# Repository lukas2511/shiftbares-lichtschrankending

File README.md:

# shiftbares-lichtschrankending

Lichtschranken-Platine für unsere Fledermauslichtschranken

Bauteile:
- 8x Phototransistor (??)
- 8x IR-LED (??)
- 8x 100 Ohm (Vorwiderstand für LEDs)
- 8x 10 kOhm (Pull-Up für Phototransistoren)
- 1x 74HC595 (Shift-Register, U74HC595AG, DIP-16)
- 2x 74HC4066 (4-fach Analog-Schalter, M74HC4066B1R, DIP-14)
- 1x BC337 (NPN Transistor, TO-92)
- 1x 1000µF Kondensator (Radial, schräg montiert -> exakte Größe egal)
- 1x 10-pin 2.54mm Stiftleiste 90°-Winkel
- 1x 10-pin 2.54mm Buchsenleiste 90°-Winkel

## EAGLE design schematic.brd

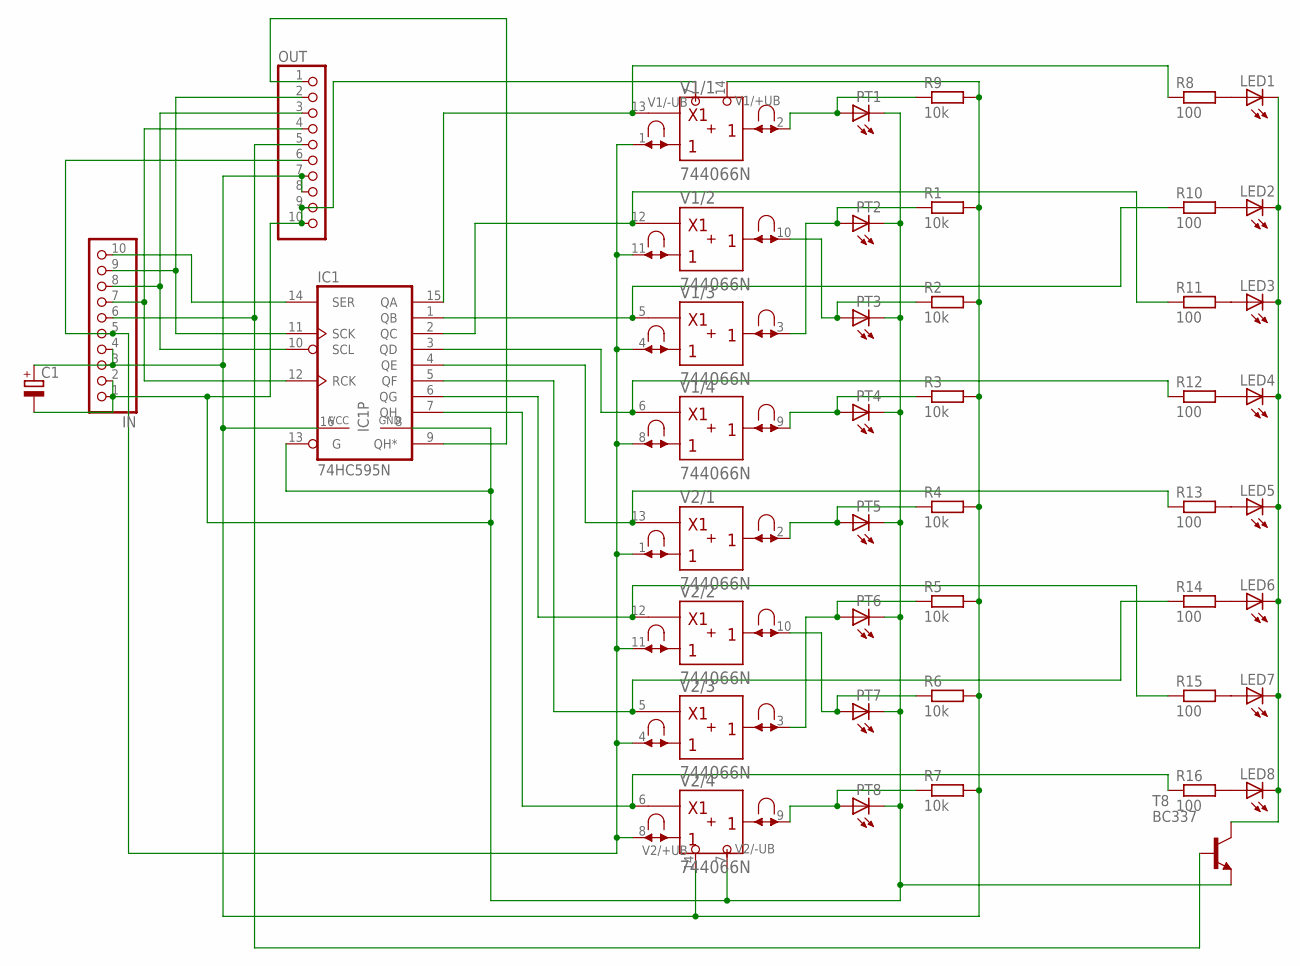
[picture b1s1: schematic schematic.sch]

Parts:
C1: CPOL-EUE5-10.5; E5-10,5
IC1: 74HC595N; DIL16
IN: PINHD-1X10/90; 1X10/90
LED1, LED2, LED3, LED4, LED5, LED6, LED7, LED8: LED5MM
OUT: PINHD-1X10/90; 1X10/90
PT1, PT2, PT3, PT4, PT5, PT6, PT7, PT8: LED5MM
R1, R2, R3, R4, R5, R6, R7, R9: 10k; 0204/7
R8, R10, R11, R12, R13, R14, R15, R16: 100; 0204/7
T8: BC337; TO92
V1, V2: 744066N; DIL14

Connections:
GND: C1.-, IC1.8 (GND), IC1.13 (G), IN.1, IN.2, OUT.9, OUT.10, PT1.K (C), PT2.K (C), PT3.K (C), PT4.K (C), PT5.K (C), PT6.K (C), PT7.K (C), PT8.K (C), T8.1 (E), V1.7 (-UB), V2.7 (-UB)
unnamed: IC1.15 (QA), R8.1, V1.13 (C)
unnamed: IC1.5 (QF), R14.1, V2.5 (C)
unnamed: IN.6, OUT.5, T8.2 (B)
unnamed: IC1.3 (QD), R12.1, V1.6 (C)
unnamed: IC1.4 (QE), R13.1, V2.13 (C)
unnamed: IC1.6 (QG), R15.1, V2.12 (C)
unnamed: IC1.7 (QH), R16.1, V2.6 (C)
unnamed: IC1.9 (QH*), OUT.1
unnamed: IC1.1 (QB), R10.1, V1.5 (C)
unnamed: PT8.A, R7.1, V2.9 (B)
unnamed: PT7.A, R6.1, V2.10 (B)
unnamed: PT6.A, R5.1, V2.3 (B)
unnamed: PT5.A, R4.1, V2.2 (B)
unnamed: PT4.A, R3.1, V1.9 (B)
unnamed: PT3.A, R2.1, V1.10 (B)
unnamed: PT2.A, R1.1, V1.3 (B)
unnamed: PT1.A, R9.1, V1.2 (B)
unnamed: LED1.A, R8.2
unnamed: IC1.10 (SCL), IN.8, OUT.3
unnamed: IC1.12 (RCK), IN.7, OUT.4
unnamed: LED2.A, R10.2
unnamed: IC1.11 (SCK), IN.9, OUT.2
unnamed: IC1.14 (SER), IN.10
unnamed: LED3.A, R11.2
unnamed: LED4.A, R12.2
unnamed: LED5.A, R13.2
unnamed: LED6.A, R14.2
unnamed: LED7.A, R15.2
unnamed: LED8.A, R16.2
unnamed: LED1.K (C), LED2.K (C), LED3.K (C), LED4.K (C), LED5.K (C), LED6.K (C), LED7.K (C), LED8.K (C), T8.3 (C)
unnamed: IC1.2 (QC), R11.1, V1.12 (C)
unnamed: IN.5, OUT.6, V1.1 (A), V1.4 (A), V1.8 (A), V1.11 (A), V2.1 (A), V2.4 (A), V2.8 (A), V2.11 (A)
VCC: C1.+, IC1.16 (VCC), IN.3, IN.4, OUT.7, OUT.8, R1.2, R2.2, R3.2, R4.2, R5.2, R6.2, R7.2, R9.2, V1.14 (+UB), V2.14 (+UB)

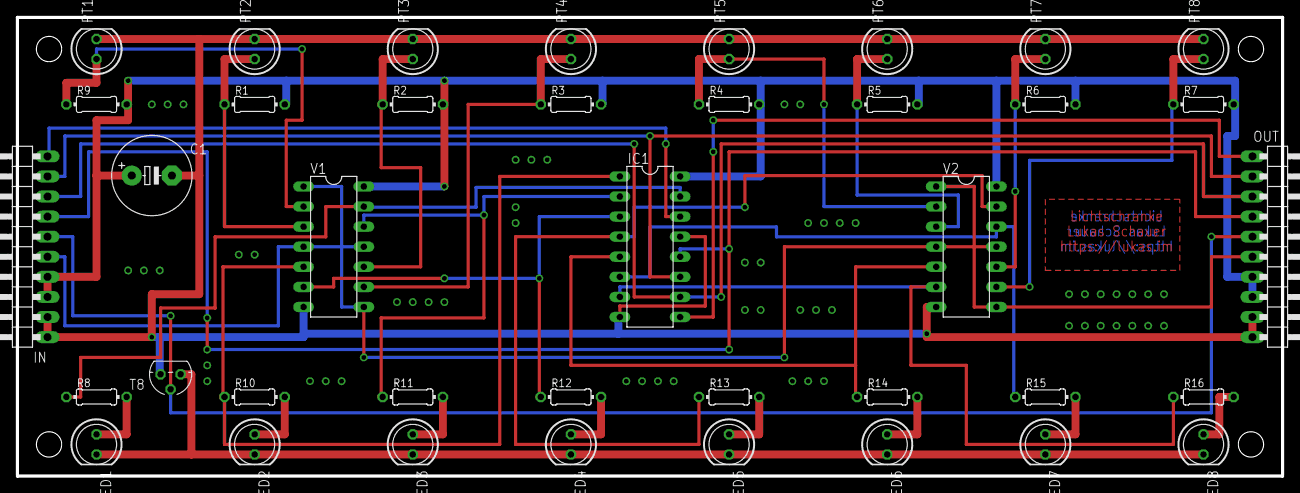
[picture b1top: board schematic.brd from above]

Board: 2 copper layers, 160.0 x 58.0 mm, 39 parts (0 on the bottom side), 34 nets.

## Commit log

2018-01-02 fixed connection to ground plane, added ground stitching, added ground plane isolation
